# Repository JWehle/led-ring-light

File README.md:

# led-ring-light
A custom LED ring light board.

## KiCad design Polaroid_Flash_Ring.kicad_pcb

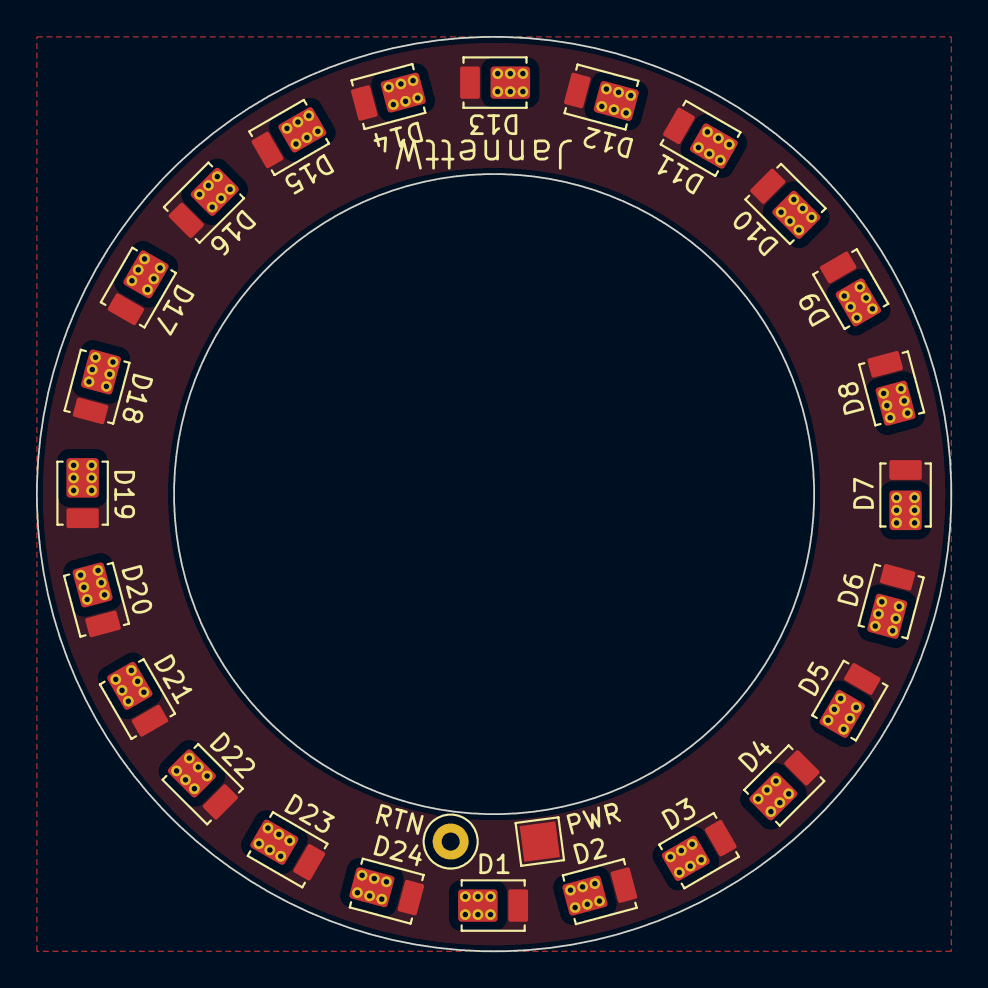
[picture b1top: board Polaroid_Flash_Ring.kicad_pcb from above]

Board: 2 copper layers, 50.8 x 50.8 mm, 26 parts (0 on the bottom side), 2 nets, no tracks yet.

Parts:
D1, D2, D3, D4, D5, D6, D7, D8, D9, D10, D11, D12, D13, D14, D15, D16, D17, D18, D19, D20, D21, D22, D23, D24: LED; CREE_J_SERIES_1113
H1: 1mm_Hole; TestPoint_Loop_D1.80mm_Drill1.0mm_Beaded
TP1: 2mm_Pad; TestPoint_Pad_2.0x2.0mm

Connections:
+6V: D1.2 (A), D2.2 (A), D3.2 (A), D4.2 (A), D5.2 (A), D6.2 (A), D7.2 (A), D8.2 (A), D9.2 (A), D10.2 (A), D11.2 (A), D12.2 (A), D13.2 (A), D14.2 (A), D15.2 (A), D16.2 (A), D17.2 (A), D18.2 (A), D19.2 (A), D20.2 (A), D21.2 (A), D22.2 (A), D23.2 (A), D24.2 (A), TP1.1
GND: D1.1 (K), D2.1 (K), D3.1 (K), D4.1 (K), D5.1 (K), D6.1 (K), D7.1 (K), D8.1 (K), D9.1 (K), D10.1 (K), D11.1 (K), D12.1 (K), D13.1 (K), D14.1 (K), D15.1 (K), D16.1 (K), D17.1 (K), D18.1 (K), D19.1 (K), D20.1 (K), D21.1 (K), D22.1 (K), D23.1 (K), D24.1 (K), H1.1
